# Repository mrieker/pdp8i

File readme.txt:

Re-implementation of a PDP-8/I processor using
currently available 74HC series DIP-form chips.
Includes extended arithmetic, 32KW memory and a
TTY interface.

Interfaces to a PiDP-8/I panel, taking the place of
the RasPI.

Optionally can use a ZTurn Zynq board to provide
additional I/O device emulation and TCL script
console access.  The Zynq also contains Verilog
equivalents of the circuit boards so can be used
for debugging and testing the board designs and
software with or without the physical circuit
boards.

Must have either the PiDP-8/I panel or the Zynq
board or both.

The circuit is a re-design using currently available
74AC, 74AHC and 74HC series chips.  It uses a 10MHz
signal for timing instead of delay lines.  It
preserves the TS1,TS2,TS3,TS4 timing states for the
most part.  In this design, TS1 takes 300nS (three
10MHz cycles), TS2,3,4 each take 400nS (four 10MHz
cycles), giving an overall cycle time of 1.5uS.

    TS1 - read memory into MBUF
    TS2 - compute memory update into MBUF
    TS3 - write memory from MBUF
          compute then write ACUM,LINK update
    TS4 - compute next major state
          including extended memory address

    The corresponding TPn occurs during last 100nS of
    the TSn.

If present, the ZTurn board provides the 10MHz signal,
allowing the Zynq full control of the clock for testing.
Otherwise it must on a separate board.

I/O instructions are also 1.5uS instead of being extended
to 4.25uS.  There is just one io pulse regardless of the
low three opcode bits that occurs starting 100nS into TS2
and ends at end of TS3.  I/O devices can use TP2 or TP3 to
clock data coming from the processor (from ACUM bus lines).
The processor clocks data from the I/O device (ACCLEAR,
INBUS, IOSKIP bus lines) at TP3.  An I/O device can extend
TS3 by asserting PAUSE starting in TS2.

The major states are the same (FETCH, DEFER, EXEC, WRDCT,
CURAD, BREAK), but with the addition of:

    INTAK - save and clear DF,IF registers, write PC to 00000,
            clear interrupt enable, jump to 00001
    DEPOS - do memory write in response to DEP switch
    EXAM  - do memory read in response to LDAD or EXAM switch

When halted, all four of TS1,2,3,4 are negated.  The state
info in the registers indicates what is going to happen next,
as halting occurs at the end of TS4 which establishes the next
major state.  Pressing CONT will start TS1 with whatever is in
the registers.

Directories:

    ccode    - C programs that run on the Zynq
    demos    - some PDP-8/I programs
    edu20c   - edusystem 20 basic
    kicads   - circuit boards
    verisim  - Verilator for testing circuit design
    zplin    - Zynq compatible Linux (softlink to pdp8l repo zplin)
    zynq     - Zynq Verilog code

Website:  https://www.outerworldapps.com/8ipics/

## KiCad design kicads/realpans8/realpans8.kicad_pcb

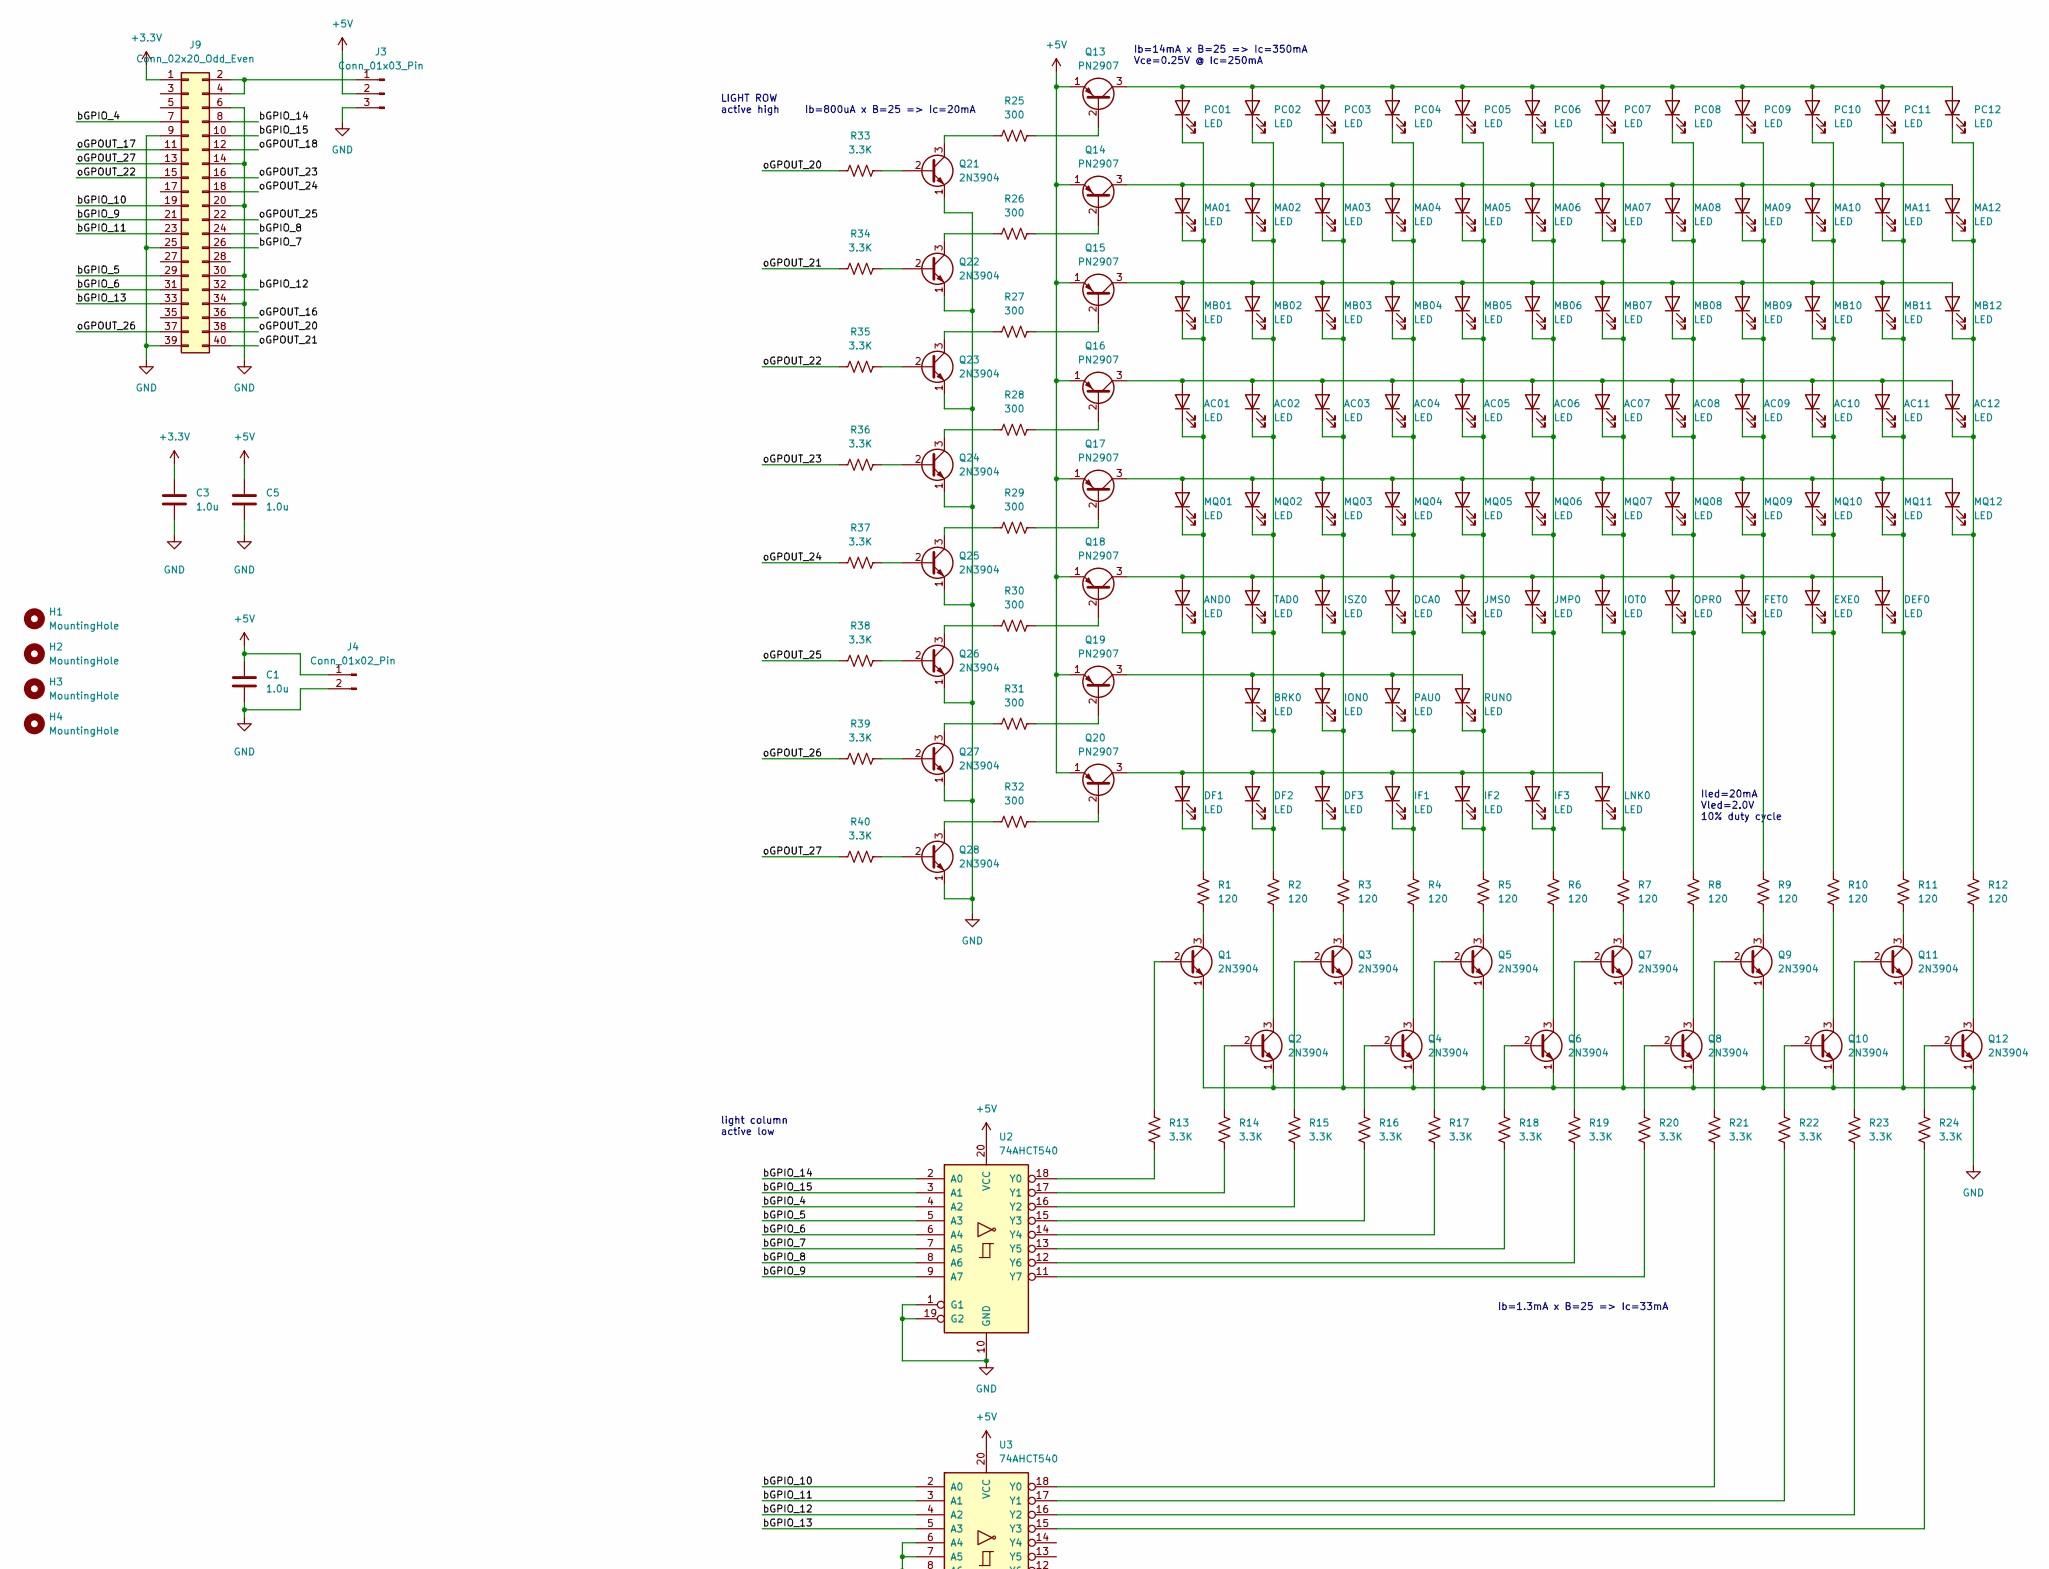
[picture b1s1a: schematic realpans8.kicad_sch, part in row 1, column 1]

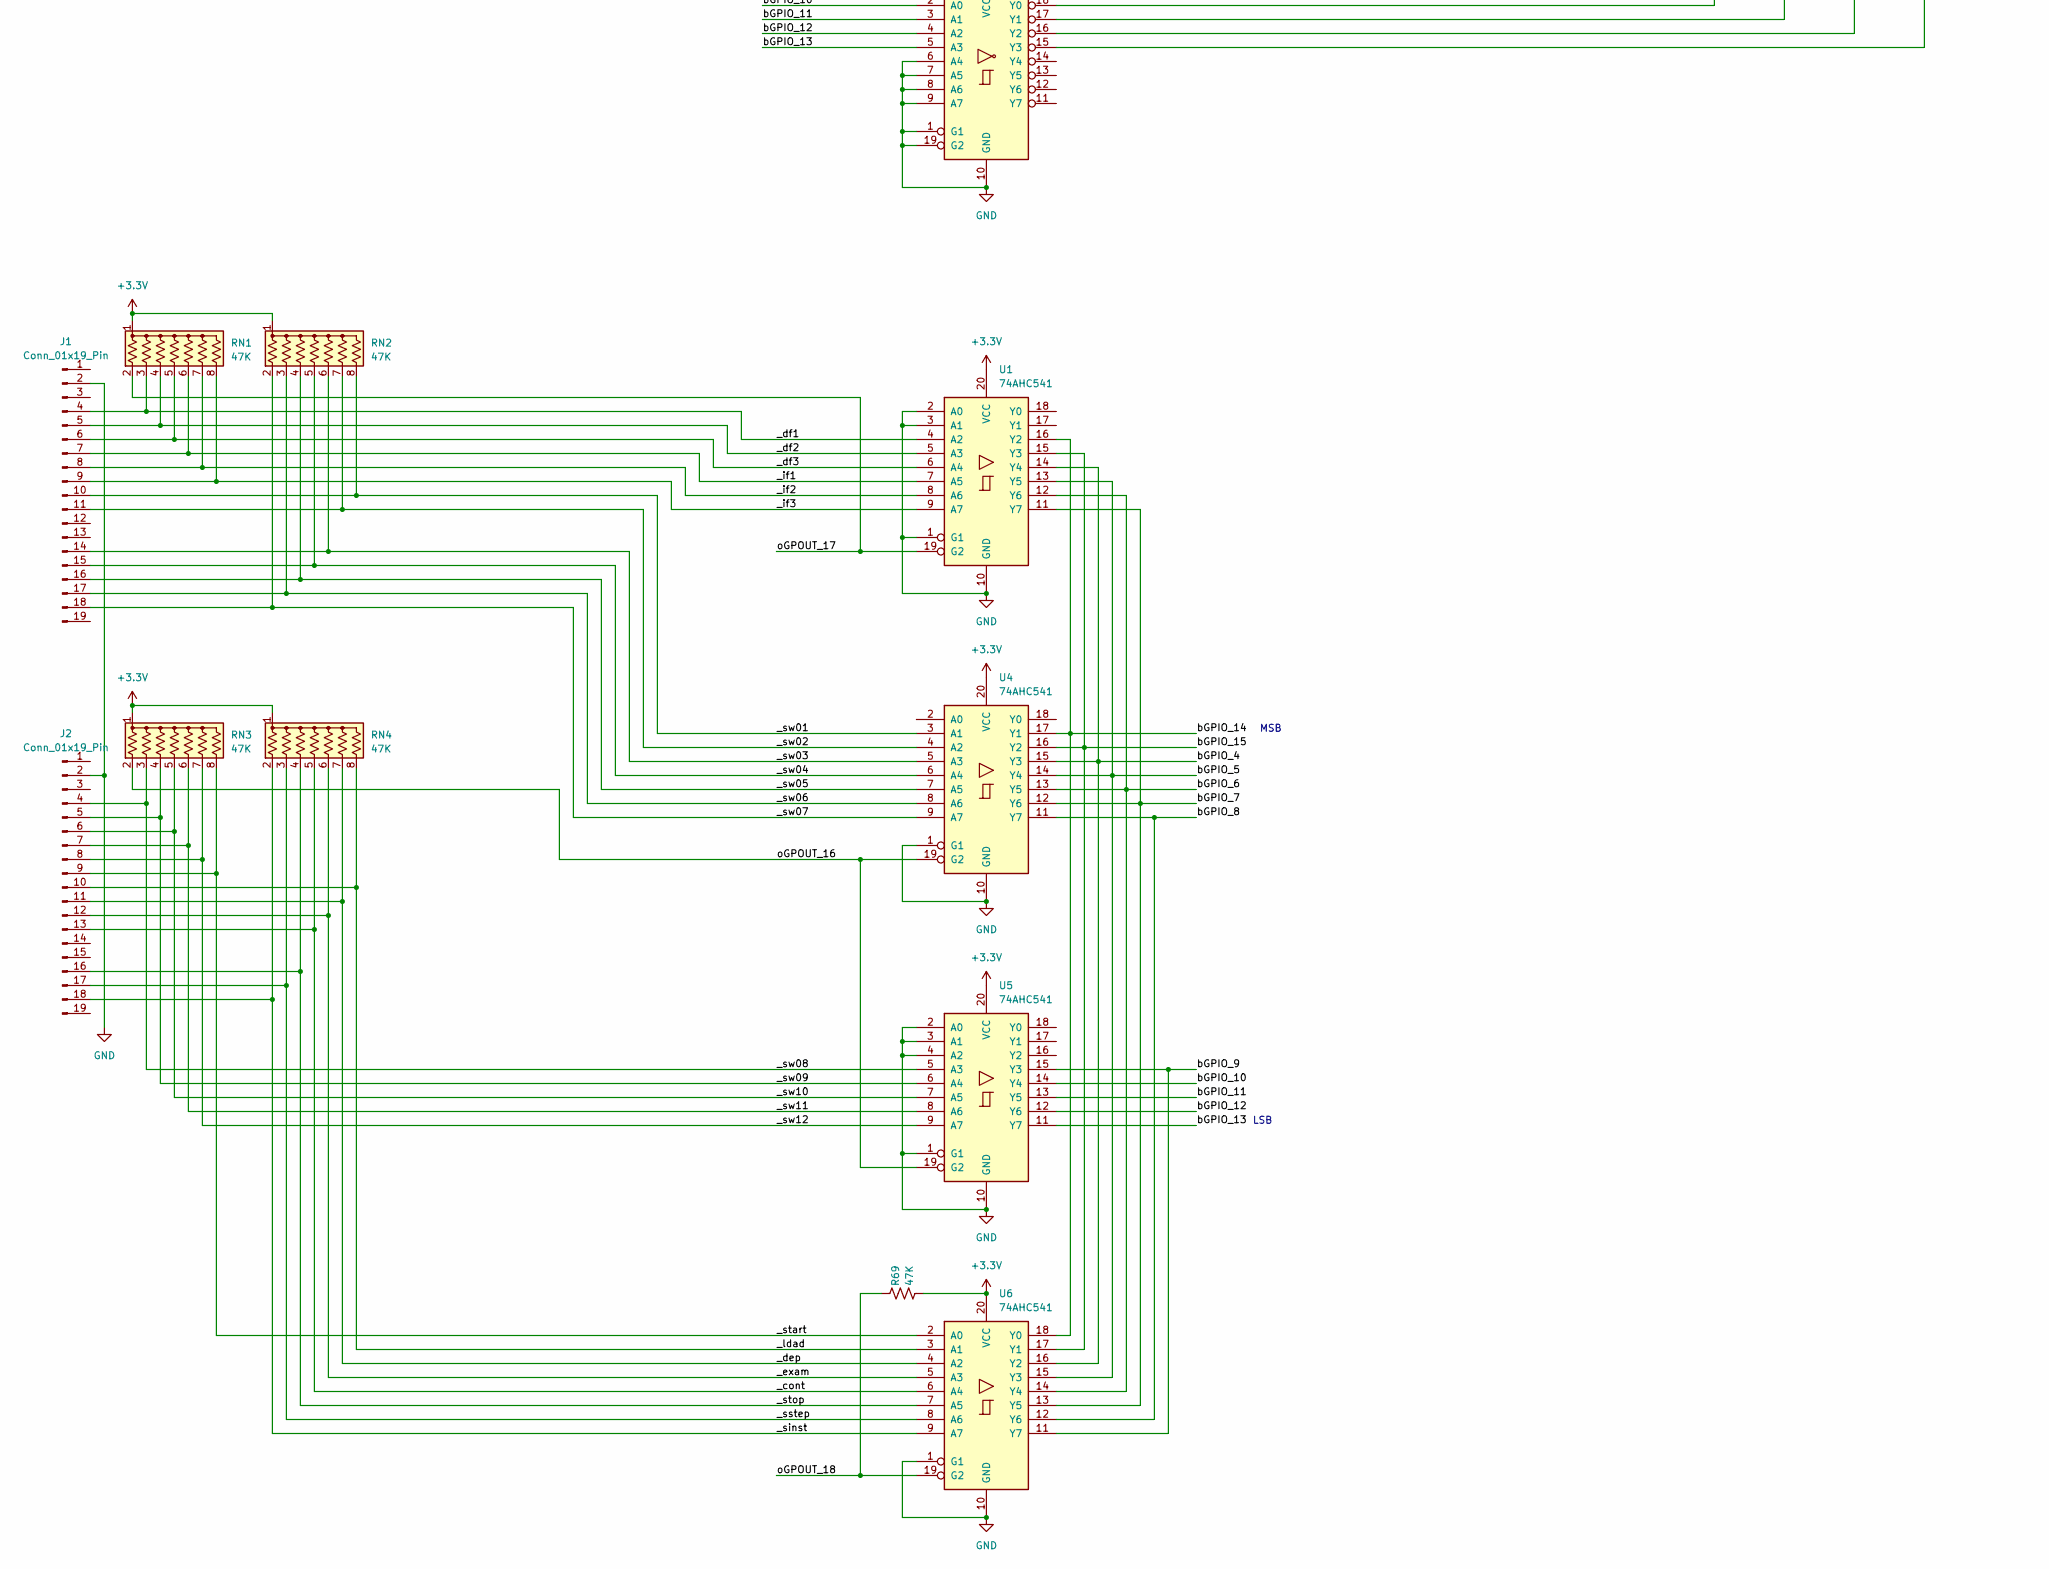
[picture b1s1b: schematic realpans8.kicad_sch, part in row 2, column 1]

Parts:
AC01, AC02, AC03, AC04, AC05, AC06, AC07, AC08, AC09, AC10, AC11, AC12: LED; LED_D5.0mm
AND0: LED; LED_D5.0mm
BRK0: LED; LED_D5.0mm
C1, C3, C5: 1.0u; R_Axial_DIN0207_L6.3mm_D2.5mm_P7.62mm_Horizontal
DCA0: LED; LED_D5.0mm
DEF0: LED; LED_D5.0mm
DF1, DF2, DF3: LED; LED_D5.0mm
EXE0: LED; LED_D5.0mm
FET0: LED; LED_D5.0mm
H1, H2, H3, H4: MountingHole; MountingHole_4.5mm
IF1, IF2, IF3: LED; LED_D5.0mm
ION0: LED; LED_D5.0mm
IOT0: LED; LED_D5.0mm
ISZ0: LED; LED_D5.0mm
J1, J2: Conn_01x19_Pin; PinHeader_1x19_P2.54mm_Vertical
J3: Conn_01x03_Pin; PinHeader_1x03_P2.54mm_Vertical
J4: Conn_01x02_Pin; PinHeader_1x02_P2.54mm_Vertical
J9: Conn_02x20_Odd_Even; PinHeader_2x20_P2.54mm_Vertical
JMP0: LED; LED_D5.0mm
JMS0: LED; LED_D5.0mm
LNK0: LED; LED_D5.0mm
MA01, MA02, MA03, MA04, MA05, MA06, MA07, MA08, MA09, MA10, MA11, MA12: LED; LED_D5.0mm
MB01, MB02, MB03, MB04, MB05, MB06, MB07, MB08, MB09, MB10, MB11, MB12: LED; LED_D5.0mm
MQ01, MQ02, MQ03, MQ04, MQ05, MQ06, MQ07, MQ08, MQ09, MQ10, MQ11, MQ12: LED; LED_D5.0mm
OPR0: LED; LED_D5.0mm
PAU0: LED; LED_D5.0mm
PC01, PC02, PC03, PC04, PC05, PC06, PC07, PC08, PC09, PC10, PC11, PC12: LED; LED_D5.0mm
Q1, Q2, Q3, Q4, Q5, Q6, Q7, Q8, Q9, Q10, Q11, Q12, Q21, Q22, Q23, Q24, Q25, Q26, Q27, Q28: 2N3904; TO-92_Wide
Q13, Q14, Q15, Q16, Q17, Q18, Q19, Q20: PN2907; TO-92_Wide
R1, R2, R3, R4, R5, R6, R7, R8, R9, R10, R11, R12: 120; R_Axial_DIN0207_L6.3mm_D2.5mm_P7.62mm_Horizontal
R13, R14, R15, R16, R17, R18, R19, R20, R21, R22, R23, R24, R33, R34, R35, R36, R37, R38, R39, R40: 3.3K; R_Axial_DIN0207_L6.3mm_D2.5mm_P7.62mm_Horizontal
R25, R26, R27, R28, R29, R30, R31, R32: 300; R_Axial_DIN0207_L6.3mm_D2.5mm_P7.62mm_Horizontal
R69: 47K; R_Axial_DIN0207_L6.3mm_D2.5mm_P7.62mm_Horizontal
RN1, RN2, RN3, RN4: 47K; R_Array_SIP8
RUN0: LED; LED_D5.0mm
TAD0: LED; LED_D5.0mm
U1, U4, U5, U6: 74AHC541; DIP-20_W7.62mm
U2, U3: 74AHCT540; DIP-20_W7.62mm

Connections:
+3.3V: C3.1, J9.1, R69.1, RN1.1 (common), RN2.1 (common), RN3.1 (common), RN4.1 (common), U1.20 (VCC), U4.20 (VCC), U5.20 (VCC), U6.20 (VCC)
+5V: C1.1, C5.1, J3.2, J4.1, Q13.1 (E), Q14.1 (E), Q15.1 (E), Q16.1 (E), Q17.1 (E), Q18.1 (E), Q19.1 (E), Q20.1 (E), U2.20 (VCC), U3.20 (VCC)
/_cont: J2.13, RN4.5 (R4), U6.6 (A4)
/_dep: J2.11, RN4.7 (R6), U6.4 (A2)
/_df1: J1.4, RN1.3 (R2), U1.4 (A2)
/_df2: J1.5, RN1.4 (R3), U1.5 (A3)
/_df3: J1.6, RN1.5 (R4), U1.6 (A4)
/_exam: J2.12, RN4.6 (R5), U6.5 (A3)
/_if1: J1.7, RN1.6 (R5), U1.7 (A5)
/_if2: J1.8, RN1.7 (R6), U1.8 (A6)
/_if3: J1.9, RN1.8 (R7), U1.9 (A7)
/_ldad: J2.10, RN4.8 (R7), U6.3 (A1)
/_sinst: J2.18, RN4.2 (R1), U6.9 (A7)
/_sstep: J2.17, RN4.3 (R2), U6.8 (A6)
/_start: J2.9, RN3.8 (R7), U6.2 (A0)
/_stop: J2.16, RN4.4 (R3), U6.7 (A5)
/_sw01: J1.10, RN2.8 (R7), U4.3 (A1)
/_sw02: J1.11, RN2.7 (R6), U4.4 (A2)
/_sw03: J1.14, RN2.6 (R5), U4.5 (A3)
/_sw04: J1.15, RN2.5 (R4), U4.6 (A4)
/_sw05: J1.16, RN2.4 (R3), U4.7 (A5)
/_sw06: J1.17, RN2.3 (R2), U4.8 (A6)
/_sw07: J1.18, RN2.2 (R1), U4.9 (A7)
/_sw08: J2.4, RN3.3 (R2), U5.5 (A3)
/_sw09: J2.5, RN3.4 (R3), U5.6 (A4)
/_sw10: J2.6, RN3.5 (R4), U5.7 (A5)
/_sw11: J2.7, RN3.6 (R5), U5.8 (A6)
/_sw12: J2.8, RN3.7 (R6), U5.9 (A7)
/bGPIO_4: J9.7, U1.14 (Y4), U2.4 (A2), U4.15 (Y3), U6.16 (Y2)
/bGPIO_5: J9.29, U1.13 (Y5), U2.5 (A3), U4.14 (Y4), U6.15 (Y3)
/bGPIO_6: J9.31, U1.12 (Y6), U2.6 (A4), U4.13 (Y5), U6.14 (Y4)
/bGPIO_7: J9.26, U1.11 (Y7), U2.7 (A5), U4.12 (Y6), U6.13 (Y5)
/bGPIO_8: J9.24, U2.8 (A6), U4.11 (Y7), U6.12 (Y6)
/bGPIO_9: J9.21, U2.9 (A7), U5.15 (Y3), U6.11 (Y7)
/bGPIO_10: J9.19, U3.2 (A0), U5.14 (Y4)
/bGPIO_11: J9.23, U3.3 (A1), U5.13 (Y5)
/bGPIO_12: J9.32, U3.4 (A2), U5.12 (Y6)
/bGPIO_13: J9.33, U3.5 (A3), U5.11 (Y7)
/bGPIO_14: J9.8, U1.16 (Y2), U2.2 (A0), U4.17 (Y1), U6.18 (Y0)
/bGPIO_15: J9.10, U1.15 (Y3), U2.3 (A1), U4.16 (Y2), U6.17 (Y1)
/oGPOUT_16: J9.36, RN3.2 (R1), U4.19 (G2), U5.19 (G2)
/oGPOUT_17: J9.11, RN1.2 (R1), U1.19 (G2)
/oGPOUT_18: J9.12, R69.2, U6.19 (G2)
/oGPOUT_20: J9.38, R33.1
/oGPOUT_21: J9.40, R34.1
/oGPOUT_22: J9.15, R35.1
/oGPOUT_23: J9.16, R36.1
/oGPOUT_24: J9.18, R37.1
/oGPOUT_25: J9.22, R38.1
/oGPOUT_26: J9.37, R39.1
/oGPOUT_27: J9.13, R40.1
GND: C1.2, C3.2, C5.2, J1.2, J2.2, J3.3, J4.2, J9.6, J9.9, J9.14, J9.20, J9.25, J9.30, J9.34, J9.39, Q1.1 (E), Q2.1 (E), Q3.1 (E), Q4.1 (E), Q5.1 (E), Q6.1 (E), Q7.1 (E), Q8.1 (E), Q9.1 (E), Q10.1 (E), Q11.1 (E), Q12.1 (E), Q21.1 (E), Q22.1 (E), Q23.1 (E), Q24.1 (E), Q25.1 (E), Q26.1 (E), Q27.1 (E), Q28.1 (E), U1.1 (G1), U1.2 (A0), U1.3 (A1), U1.10 (GND), U2.1 (G1), U2.10 (GND), U2.19 (G2), U3.1 (G1), U3.6 (A4), U3.7 (A5), U3.8 (A6), U3.9 (A7), U3.10 (GND), U3.19 (G2), U4.1 (G1), U4.10 (GND), U5.1 (G1), U5.2 (A0), U5.3 (A1), U5.4 (A2), U5.10 (GND), U6.1 (G1), U6.10 (GND)
unnamed: AC01.2 (A), AC02.2 (A), AC03.2 (A), AC04.2 (A), AC05.2 (A), AC06.2 (A), AC07.2 (A), AC08.2 (A), AC09.2 (A), AC10.2 (A), AC11.2 (A), AC12.2 (A), Q16.3 (C)
unnamed: AC01.1 (K), AND0.1 (K), DF1.1 (K), MA01.1 (K), MB01.1 (K), MQ01.1 (K), PC01.1 (K), R1.1
unnamed: AC02.1 (K), BRK0.1 (K), DF2.1 (K), MA02.1 (K), MB02.1 (K), MQ02.1 (K), PC02.1 (K), R2.1, TAD0.1 (K)
unnamed: AC03.1 (K), DF3.1 (K), ION0.1 (K), ISZ0.1 (K), MA03.1 (K), MB03.1 (K), MQ03.1 (K), PC03.1 (K), R3.1
unnamed: AC04.1 (K), DCA0.1 (K), IF1.1 (K), MA04.1 (K), MB04.1 (K), MQ04.1 (K), PAU0.1 (K), PC04.1 (K), R4.1
unnamed: AC05.1 (K), IF2.1 (K), JMS0.1 (K), MA05.1 (K), MB05.1 (K), MQ05.1 (K), PC05.1 (K), R5.1, RUN0.1 (K)
unnamed: AC06.1 (K), IF3.1 (K), JMP0.1 (K), MA06.1 (K), MB06.1 (K), MQ06.1 (K), PC06.1 (K), R6.1
unnamed: AC07.1 (K), IOT0.1 (K), LNK0.1 (K), MA07.1 (K), MB07.1 (K), MQ07.1 (K), PC07.1 (K), R7.1
unnamed: AC08.1 (K), MA08.1 (K), MB08.1 (K), MQ08.1 (K), OPR0.1 (K), PC08.1 (K), R8.1
unnamed: AC09.1 (K), FET0.1 (K), MA09.1 (K), MB09.1 (K), MQ09.1 (K), PC09.1 (K), R9.1
unnamed: AC10.1 (K), EXE0.1 (K), MA10.1 (K), MB10.1 (K), MQ10.1 (K), PC10.1 (K), R10.1
unnamed: AC11.1 (K), DEF0.1 (K), MA11.1 (K), MB11.1 (K), MQ11.1 (K), PC11.1 (K), R11.1
unnamed: AC12.1 (K), MA12.1 (K), MB12.1 (K), MQ12.1 (K), PC12.1 (K), R12.1
unnamed: AND0.2 (A), DCA0.2 (A), DEF0.2 (A), EXE0.2 (A), FET0.2 (A), IOT0.2 (A), ISZ0.2 (A), JMP0.2 (A), JMS0.2 (A), OPR0.2 (A), Q18.3 (C), TAD0.2 (A)
unnamed: BRK0.2 (A), ION0.2 (A), PAU0.2 (A), Q19.3 (C), RUN0.2 (A)
unnamed: DF1.2 (A), DF2.2 (A), DF3.2 (A), IF1.2 (A), IF2.2 (A), IF3.2 (A), LNK0.2 (A), Q20.3 (C)
unnamed: J3.1, J9.2, J9.4
unnamed: MA01.2 (A), MA02.2 (A), MA03.2 (A), MA04.2 (A), MA05.2 (A), MA06.2 (A), MA07.2 (A), MA08.2 (A), MA09.2 (A), MA10.2 (A), MA11.2 (A), MA12.2 (A), Q14.3 (C)
unnamed: MB01.2 (A), MB02.2 (A), MB03.2 (A), MB04.2 (A), MB05.2 (A), MB06.2 (A), MB07.2 (A), MB08.2 (A), MB09.2 (A), MB10.2 (A), MB11.2 (A), MB12.2 (A), Q15.3 (C)
unnamed: MQ01.2 (A), MQ02.2 (A), MQ03.2 (A), MQ04.2 (A), MQ05.2 (A), MQ06.2 (A), MQ07.2 (A), MQ08.2 (A), MQ09.2 (A), MQ10.2 (A), MQ11.2 (A), MQ12.2 (A), Q17.3 (C)
unnamed: PC01.2 (A), PC02.2 (A), PC03.2 (A), PC04.2 (A), PC05.2 (A), PC06.2 (A), PC07.2 (A), PC08.2 (A), PC09.2 (A), PC10.2 (A), PC11.2 (A), PC12.2 (A), Q13.3 (C)
unnamed: Q1.2 (B), R13.1
unnamed: Q1.3 (C), R1.2
unnamed: Q2.2 (B), R14.1
unnamed: Q2.3 (C), R2.2
unnamed: Q3.2 (B), R15.1
unnamed: Q3.3 (C), R3.2
unnamed: Q4.2 (B), R16.1
unnamed: Q4.3 (C), R4.2
unnamed: Q5.2 (B), R17.1
unnamed: Q5.3 (C), R5.2
unnamed: Q6.2 (B), R18.1
unnamed: Q6.3 (C), R6.2
unnamed: Q7.2 (B), R19.1
unnamed: Q7.3 (C), R7.2
unnamed: Q8.2 (B), R20.1
unnamed: Q8.3 (C), R8.2
unnamed: Q9.2 (B), R21.1
unnamed: Q9.3 (C), R9.2
unnamed: Q10.2 (B), R22.1
unnamed: Q10.3 (C), R10.2
unnamed: Q11.2 (B), R23.1
unnamed: Q11.3 (C), R11.2
unnamed: Q12.2 (B), R24.1
unnamed: Q12.3 (C), R12.2
unnamed: Q13.2 (B), R25.2
unnamed: Q14.2 (B), R26.2
unnamed: Q15.2 (B), R27.2
unnamed: Q16.2 (B), R28.2
unnamed: Q17.2 (B), R29.2
unnamed: Q18.2 (B), R30.2
unnamed: Q19.2 (B), R31.2
unnamed: Q20.2 (B), R32.2
unnamed: Q21.2 (B), R33.2
unnamed: Q21.3 (C), R25.1
unnamed: Q22.2 (B), R34.2
unnamed: Q22.3 (C), R26.1
unnamed: Q23.2 (B), R35.2
unnamed: Q23.3 (C), R27.1
unnamed: Q24.2 (B), R36.2
unnamed: Q24.3 (C), R28.1
unnamed: Q25.2 (B), R37.2
unnamed: Q25.3 (C), R29.1
unnamed: Q26.2 (B), R38.2
unnamed: Q26.3 (C), R30.1
unnamed: Q27.2 (B), R39.2
unnamed: Q27.3 (C), R31.1
unnamed: Q28.2 (B), R40.2
unnamed: Q28.3 (C), R32.1
unnamed: R13.2, U2.18 (Y0)
unnamed: R14.2, U2.17 (Y1)
unnamed: R15.2, U2.16 (Y2)
unnamed: R16.2, U2.15 (Y3)
unnamed: R17.2, U2.14 (Y4)
unnamed: R18.2, U2.13 (Y5)
unnamed: R19.2, U2.12 (Y6)
unnamed: R20.2, U2.11 (Y7)
unnamed: R21.2, U3.18 (Y0)
unnamed: R22.2, U3.17 (Y1)
unnamed: R23.2, U3.16 (Y2)
unnamed: R24.2, U3.15 (Y3)

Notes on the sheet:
Ib=1.3mA x B=25 => Ic=33mA
Iled=20mA Vled=2.0V 10% duty cycle
Ib=800uA x B=25 => Ic=20mA
MSB
Ib=14mA x B=25 => Ic=350mA Vce=0.25V @ Ic=250mA
LIGHT ROW active high
light column active low
LSB

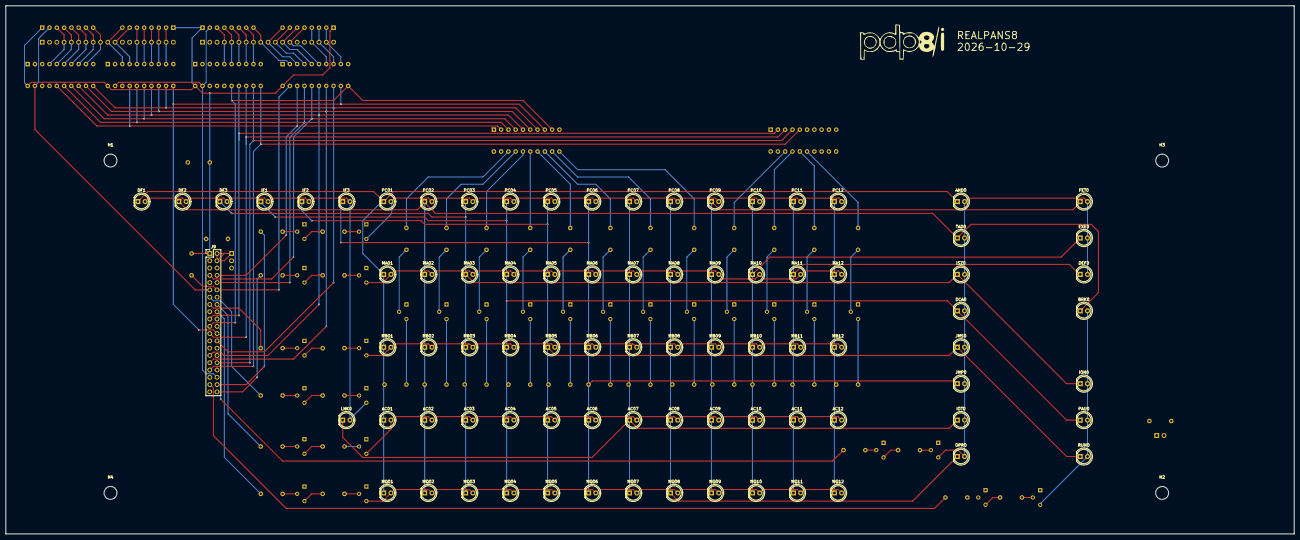
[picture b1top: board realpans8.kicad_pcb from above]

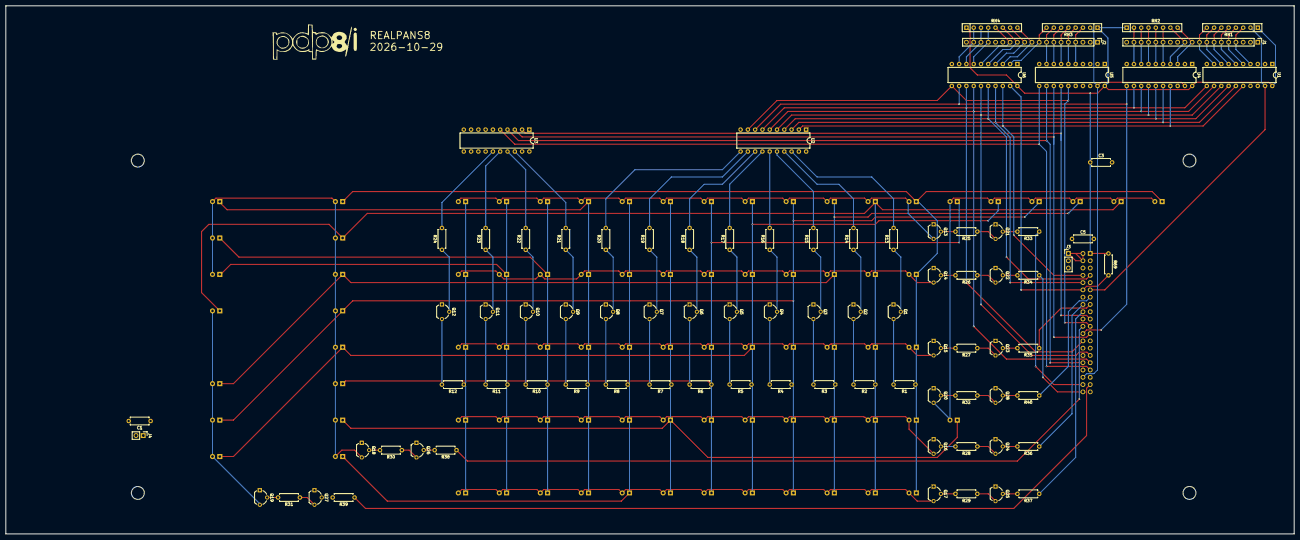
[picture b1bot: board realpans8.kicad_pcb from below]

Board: 4 copper layers, 449.3 x 184.2 mm, 173 parts (86 on the bottom side), 133 nets.

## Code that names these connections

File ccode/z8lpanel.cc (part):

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        // read bulbs and switches
        padlib->readpads (&pads);

        bool irand = pads.light.ir == 0;
        bool irtad = pads.light.ir == 1;
        bool irisz = pads.light.ir == 2;
        bool irdca = pads.light.ir == 3;
        bool irjms = pads.light.ir == 4;
        bool irjmp = pads.light.ir == 5;
        bool iriot = pads.light.ir == 6;
        bool iropr = pads.light.ir == 7;

        bool msfet = pads.light.ms == MS_FETCH;
        bool msdef = pads.light.ms == MS_DEFER;
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
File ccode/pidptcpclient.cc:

//    Copyright (C) Mike Rieker, Beverly, MA USA
//    www.outerworldapps.com
//
//    This program is free software; you can redistribute it and/or modify
//    it under the terms of the GNU General Public License as published by
//    the Free Software Foundation; version 2 of the License.
//
//    This program is distributed in the hope that it will be useful,
//    but WITHOUT ANY WARRANTY; without even the implied warranty of
//    MERCHANTABILITY or FITNESS FOR A PARTICULAR PURPOSE.  See the
//    GNU General Public License for more details.
//
//    EXPECT it to FAIL when someone's HeALTh or PROpeRTy is at RISk.
//
//    You should have received a copy of the GNU General Public License
//    along with this program; if not, write to the Free Software
//    Foundation, Inc., 59 Temple Place, Suite 330, Boston, MA  02111-1307  USA
//
//    http://www.gnu.org/licenses/gpl-2.0.html

// runs on zynq to send lights to and receive switches from raspi plugged into pidp8i panel
// this is a different pidp8i panel than one plugged into console.kicad_sch board

// on raspi:
//  ./pidptcpserver

// on zynq:
//  ./pidptcpclient [-nomqsc] <raspihostname>

#include <signal.h>
#include <string.h>
#include <time.h>

#include "i2czlib.h"
#include "pidp.h"
#include "z8idefs.h"

// gpio pins

                    //  LR1 LR2 LR3 LR4 LR5 LR6 LR7 LR8 SR1 SR2 SR3
#define COL1    14  //  pc1 ma1 mb1 ac1 mq1 and cad df1 sw1 df1 start   [MSB]
#define COL2    15  //  pc2 ma2 mb2 ac2 mq2 tad brk df2 sw2 df2 ldaddr
#define COL3     4  //  pc3 ma3 mb3 ac3 mq3 isz ion df3 sw3 df3 dep
#define COL4     5  //   .   .   .   .   .  dca pau if1  .  if1 exam
#define COL5     6  //   .   .   .   .   .  jms run if2  .  if2 cont
#define COL6     7  //   .   .   .   .   .  jmp sc1 if3  .  if3 stop
#define COL7     8  //   .   .   .   .   .  iot sc2 lnk  .      sstep
#define COL8     9  //   .   .   .   .   .  opr sc3      .      sinst
#define COL9    10  //   .   .   .   .   .  fet sc4      .
#define COL10   11  //   .   .   .   .   .  exe sc5      .
#define COL11   12  //   .   .   .   .   .  def          .
#define COL12   13  //   .   .   .   .   .  wct          .              [LSB]

#define COLMIN 4

static bool volatile ctrlcflag;
static uint16_t ledscrams[4096];
static uint16_t opcodeleds[8];
static uint16_t swunscrams[65536>>COLMIN];

static void siginthand (int signum);

int main (int argc, char **argv)
{
    setlinebuf (stdout);

    bool nomqsc = false;
    char const *server = NULL;
    for (int i = 0; ++ i < argc;) {
        if (strcasecmp (argv[i], "-nomqsc") == 0) {
            nomqsc = true;
            continue;
        }
        if (argv[i][0] == '-') {
            fprintf (stderr, "unknown option %s\n", argv[i]);
            return 1;
        }
        if (server != NULL) {
            fprintf (stderr, "unknown parameter %s\n", argv[i]);
            return 1;
        }
        server = argv[i];
    }
    if (server == NULL) {
        fprintf (stderr, "missing server hostname\n");
        return 1;
    }
    pidp_open (server);

    opcodeleds[0] = 1 << COL1;
    opcodeleds[1] = 1 << COL2;
    opcodeleds[2] = 1 << COL3;
    opcodeleds[3] = 1 << COL4;
    opcodeleds[4] = 1 << COL5;
    opcodeleds[5] = 1 << COL6;
    opcodeleds[6] = 1 << COL7;
    opcodeleds[7] = 1 << COL8;

    for (uint16_t data = 0; data <= 07777; data ++) {
        uint16_t gpio = 0;
        if (data & 04000) gpio |= 1 << COL1;
        if (data & 02000) gpio |= 1 << COL2;
        if (data & 01000) gpio |= 1 << COL3;
        if (data & 00400) gpio |= 1 << COL4;
        if (data & 00200) gpio |= 1 << COL5;
        if (data & 00100) gpio |= 1 << COL6;
        if (data & 00040) gpio |= 1 << COL7;
        if (data & 00020) gpio |= 1 << COL8;
        if (data & 00010) gpio |= 1 << COL9;
        if (data & 00004) gpio |= 1 << COL10;
        if (data & 00002) gpio |= 1 << COL11;
        if (data & 00001) gpio |= 1 << COL12;
        ledscrams[data] = gpio;
        swunscrams[gpio>>COLMIN] = data;
    }

    // access FPGA I2C interface to console board
    I2CZLib i2czlib;
    Z8IPanel pads;
    memset (&pads, 0, sizeof pads);

    signal (SIGINT,  siginthand);
    signal (SIGTERM, siginthand);

    i2czlib.lockpads ();

    bool firstswrow = true;
    uint16_t lastswrows[3];
    memset (lastswrows, 0, sizeof lastswrows);

    PiDPMsg pidpmsg;
    memset (&pidpmsg, 0, sizeof pidpmsg);

    while (! ctrlcflag) {

        // read lights from fpga
        i2czlib.readpads (&pads, false);
        i2czlib.unlkpads ();

        // send lights over tcp to pidp panel
        pidpmsg.ledrows[0] = ledscrams[pads.light.pc];
        pidpmsg.ledrows[1] = ledscrams[pads.light.ma];
        pidpmsg.ledrows[2] = ledscrams[pads.light.mb];
        pidpmsg.ledrows[3] = ledscrams[pads.light.ac];
        if (! nomqsc) {
            pidpmsg.ledrows[4] = ledscrams[pads.light.mq];
        }

        pidpmsg.ledrows[5] =
            opcodeleds[pads.light.ir] |
            ((pads.light.ms == MS_FETCH) ? (1 << COL9)  : 0) |
            ((pads.light.ms == MS_EXEC)  ? (1 << COL10) : 0) |
            ((pads.light.ms == MS_DEFER) ? (1 << COL11) : 0) |
            ((pads.light.ms == MS_WRDCT) ? (1 << COL12) : 0);

        pidpmsg.ledrows[6] =
            ((pads.light.ms == MS_CURAD) ? (1 << COL1) : 0) |
            ((pads.light.ms == MS_BREAK) ? (1 << COL2) : 0) |
            (pads.light.ion ? (1 << COL3) : 0) |
            (pads.light.pau ? (1 << COL4) : 0) |
            (pads.light.run ? (1 << COL5) : 0);
        if (! nomqsc) {
            pidpmsg.ledrows[6] |= ledscrams[pads.light.sc<<2];
        }

        pidpmsg.ledrows[7] =
            ledscrams[(pads.light.dfld<<9)|(pads.light.ifld<<6)] |
            (pads.light.link ? (1 << COL7) : 0);

        // ... also receives switches from pidp panel
        if (! pidp_proc (&pidpmsg)) continue;

        i2czlib.lockpads ();

        // only send switches to fpga if there is a change
        // - this allows other things (like tcl scripts) to use switches
        // - and it takes over the switches only when someone is using them
        if (! firstswrow && ((pidpmsg.swrows[0] != lastswrows[0]) ||
                (pidpmsg.swrows[1] != lastswrows[1]) || (pidpmsg.swrows[2] != lastswrows[2]))) {

            // send all switches to fpga
            pads.togval.reg = swunscrams[pidpmsg.swrows[0]>>COLMIN];
            uint32_t sr2 = swunscrams[pidpmsg.swrows[1]>>COLMIN];
            pads.togval.dfld  = (sr2 >> 9) & 7;
            pads.togval.ifld  = (sr2 >> 6) & 7;
            pads.togval.sinst = (pidpmsg.swrows[2] >> COL8) & 1;
            pads.togval.sstep = (pidpmsg.swrows[2] >> COL7) & 1;
            pads.button.stop  = (pidpmsg.swrows[2] >> COL6) & 1;
            pads.button.cont  = (pidpmsg.swrows[2] >> COL5) & 1;
            pads.button.start = (pidpmsg.swrows[2] >> COL1) & 1;
            pads.button.ldad  = (pidpmsg.swrows[2] >> COL2) & 1;
            pads.button.exam  = (pidpmsg.swrows[2] >> COL4) & 1;
            pads.button.depos = (pidpmsg.swrows[2] >> COL3) & 1;
            pads.togovr.reg   = 07777;
            pads.togovr.dfld  = 7;
            pads.togovr.ifld  = 7;
            pads.togovr.sinst = true;
            pads.togovr.sstep = true;

            uint32_t now = time (NULL);
            printf ("%02u:%02u:%02u   %o %o  %04o  %s %s %s %s %s %s %s %s\n",
                now / 3600 % 24, now / 60 % 60, now % 60,
                pads.togval.dfld, pads.togval.ifld, pads.togval.reg,
                pads.button.start ? "START" : "     ",
                pads.button.ldad  ? "LDAD"  : "    ",
                pads.button.depos ? "DEPOS" : "     ",
                pads.button.exam  ? "EXAM"  : "    ",
                pads.button.cont  ? "CONT"  : "    ",
                pads.button.stop  ? "STOP"  : "    ",
                pads.togval.sstep ? "SSTEP" : "     ",
                pads.togval.sinst ? "SINST" : "     ");

            i2czlib.writepads (&pads);
        }
        firstswrow = false;
        lastswrows[0] = pidpmsg.swrows[0];
        lastswrows[1] = pidpmsg.swrows[1];
        lastswrows[2] = pidpmsg.swrows[2];
    }

    i2czlib.unlkpads ();

    return 0;
}

static void siginthand (int signum)
{
    if (ctrlcflag) exit (1);
    ctrlcflag = true;
}

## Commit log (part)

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2026-02-03 initial commit
    $ cd verisim
    $ ./verimain.x86_64
    > isztest
    > startat 0100
    > runloop 1000000
    > runloop 1000000
2026-02-04 add simtest.sh and simtest.tcl simulator test script
    runs simulator with random instructions
    also includes assemble and disassemble TCL commands
2026-02-05 fill out field selection in processor.v
2026-02-06 get HLT simtest working
    and fix IOP2/IOP4 overlap
    clean up some simtest.tcl code
2026-02-06 move randbits to C code
    seems TCL has memory leakage issues with 64-bit numbers
2026-02-07 move all address changes to TP4
    ...so memory has constant address during TS3
2026-02-07 more timing simplification
    TS1:
    read memory
    TP1:
    clock memory data into MBUF
    TS2:
    compute updates for MBUF, PCTR
2026-02-08 regroup things around in processor.v
    gather all the loading of a register together
    to make it more like an hardware implementation
2026-02-10 add extended arithmetic support to processor
    expects ext arith board to process opcode and put result on io bus by TP3
    in either FETCH (non-memory opcode) or EXEC cycle (with memory opcode)
2026-02-11 add extarith.v module and get it working
2026-02-13 clean up clock and reset signals
    clok2 = 10MHz clock signal
    reset = power-on reset signal
2026-02-15 fix iopn signal generation
    include masking with instruction bits
2026-02-26 simplify timing cycle
    just have one iop and it overlaps TS2+TS3
    ...so all cycles are 1.6uS
2026-02-26 remove jmpjms factor from intinh test in processor.v
    intinh is now cleared in TP3 but not tested until TP4
2026-03-11 eliminate prod register from extarith.v
    also adds original AC value to product
    like pdp-8/v which passes D0MB maindec
2026-03-12 get a few more instructions of simtest.sh working
2026-03-12 get a couple instructions working with verisim/simtest.sh script
2026-03-12 get more cycles working in processor.kicad_sch and registers.kicad_sch
2026-03-12 get HLT opcode to work
    CONT switch used to wipe out non-FETCH state (such as WRDCT or BREAK)
2026-03-12 get OSR working
2026-03-12 add test code for ldad,depos,exam switches
2026-03-12 combine registers onto processor circuit board
    none of the console stuff works though
    will have to rebuild it
2026-03-12 get OSR instruction working again
2026-03-12 some circuit simplifications
2026-03-12 get all switches working in processor schematic
2026-03-12 connect up power connections to chips on processor board
2026-03-12 get extmemory working
    - runs simtest.sh 80M+ cycles
    have to run make command twice (get UNOPTFLAG warnings first time)
2026-03-12 get more of extmemory board working
2026-03-12 get start button working
2026-03-14 get a little more of new extarith.v working
2026-03-15 get new extarith divide working
2026-03-15 clean up using sctr for all counting like pdp-8/e
    use descriptions in small computer handbook 1973 chap 5
2026-03-17 upadte extarith.v muxes to be more 74xx chip-like
    also rename hold => pause
2026-03-18 stretch multiply & divide cycles to 300nS
    also allow 300nS for divide overflow
2026-03-19 add extarith schematic
    doesn't work yet
2026-03-19 program in 10nS delay per gate in verilog simulation
    removed testing of extarith for now
2026-03-20 change cycles times to 120nS
    ...addition takes too long
2026-03-20 fix up console switch timing in processor
    ldad/exam/dep:
    on press,
    set up alu to generate new MADR then after 300nS pulse it in
    then after another 100nS, load new state in MAJST
    on release,
    clear HREQ to perform the cycle
2026-03-20 set TS1=300nS, TS2=500nS, TS3=500nS, TS4=300nS
    adding only done in TS2,TS3 so make them longer
    others can be short
2026-03-21 add console circuit board
    (slows simtest.tcl down quite a bit)
2026-03-22 get console board working
2026-03-24 eliminate dependency on digging latched swreg value from internal console module signals
2026-03-24 add oscillator chip to console board
    also handle net names with < = > (used by 7485)
2026-03-25 add zynq files to access backplane simulation file
2026-03-26 get zynq stuff to compile and modify verimain to access it
    don't have driver to access page yet
2026-03-26 add km-zynqpdp8i driver to access zynq register page
    runs simtest.sh on zynq
2026-03-27 remove verisim .v files that are superceded by kicad-derived .v files
2026-03-28 add tty to zynq and get lights working in verilator
2026-03-28 get pdp8itty working in verilator
2026-03-29 get D01B maindec working with verilator
2026-04-06 add mcp23017 chip to console board
    test access to 23017:
    $ ./verimain
    ;# write 32->reg 0; 45->reg 1
    > iic wr 0x40 wr 0 wr 0x32 wr 0x45
    > clk 11111
    11111
2026-04-11 get simtest.sh working with MCP23017 console chip
    export usemcp=1
    ./simtest.sh
2026-04-12 allow console mcp23017 to read panel switches
    test:
    usemcp=0 ./simtest.sh gpio connector only
    lights: bus -> muxes -> gpio -> test script
    switches: test script -> gpio -> flipflops -> bus
    usemcp=1 ./simtest.sh mcp23017 only (gpio gets lights but not switches)
    lights: bus -> muxes -> gpio,mcp23017 -> test script
2026-04-22 little fix to simtest.tcl
    defer requesting dma or interrupt
2026-04-23 merge DMADR[11:00] bus into INBUS
    DMA master only needs to output the address during TS4
    and nothing else uses INBUS during that time
2026-04-25 put buffers on all bus pins
    make the signals active low so can put pullup terminators on backplane
    doesn't work yet
2026-04-26 get a few ./simtest.sh instructions working
2026-04-26 get a few more ./simtest.sh instructions working
2026-04-27 get usemcp=1,2 modes working with simtest.sh
    need to set gpio panel connector data bits to all ones so
    they don't interfere with console.kicad_sch bGPIO data bits
2026-04-27 add BRKGNTI/BRKGNTO signals to bus
    set at TP3 of all cycles to match BRKRQST line
    cleared at TP2 in BREAK cycle
2026-05-02 have armwrite self clock so don't need to advance processor state
2026-05-02 get started on doing better gate/flipflop delays
    doesn't work
2026-05-03 get some more working with new clocking
    run with clkratio=24
    simtest.sh runs 1259 cycles
2026-05-04 account for setup time in flipflop chips
    export clkratio=40
    export testexar=1
    export usemcp=0
    ./simtest.sh
2026-05-06 add back a version of chips.v that has fixed 10nS delay
    also put cycle counter in dmatest.v for testing
2026-05-07 add BRKCYC signal to bus for DMA circuits
    glitch-free indicating break cycle in progress
    sets at beginning of TS1, clears at end of TS3
2026-05-08 small delay when switching busDFLD/busIFLD for LDAD switch
    minimize overlapping drivers
2026-05-12 rename all 74xx references to 74HCxx
    timings in chips-varns.v are for 74HCxx
    also added 74AHCxx and 74ACxx to chips-varns.v where available
2026-05-12 substitute in AHC and AC chips into circuit boards
    testing with clkratio=20, ie 10MHz
2026-05-12 get it working with 1.28uS cycles (clkratio=16)
    ...using AHC/AC/HC gates
2026-05-16 move dmatester to a circuit board
    ...so it has realistic propagation delays
    change TS1,TS2,TS3,TS4 times to 400nS each
    ...instead of 300,500,500,300nS each
    should be ok cuz of 74AC283s instead of 74HC283s
2026-05-17 make edge connectors all single-row 1x36
2026-05-17 place chips on extmemory board
2026-05-17 add backplane kicad pcb
2026-05-24 re-port pdp8l/zynq to pdp8i/zynq
2026-05-25 plug zynq into verimain's backplane
    simtest.tcl doesn't access any of its i/o devices yet
2026-05-25 add pdp8icmem circuit to zynq
    don't have any tests for it yet
2026-05-30 get verimain zynq code working with simtest.sh
    verimain compiles with boards and zynq code
    uses chips-varns.v for the chips
    simtest includes zynq pdp8ltty.v testing
    does not test zynq pdp8isim.v
    compiling zynq code with vivado from zynq directory
    compiles pdp8isim.v which uses the board files
2026-05-30 update zynq pdp8lfpi2c.v to continuously scan panel via i2c
2026-06-01 have simtest.sh test pdp8ifpi2c.v
    pdp8ifpi2c.v can be enabled (by clearing its 'manual' bit) to
    take over scanning the physical pidp panel via the console board.
    by default, the console board does the scanning via its internal
    counters.
    usefpi2c=0 ./simtest.sh use console board scanners (fast)
    usefpi2c=1 ./simtest.sh use pdp8ifpi2c.v scanners (slow)
2026-06-01 add ccode directory (copied from pdp8l/pipan8l directory)
    get zynq to compile and get z8ldump, z8lpanel to work with it
2026-06-03 have setsw wait for switch to soak into flipflops
    also merge pipan8lini.tcl into z8lpanelini.tcl
2026-06-05 get zynq stuff compiling
    sim mode doesn't work
2026-06-06 get zynq to run something
    $ ./z8lpanel
    z8lpanel> simon
    z8lpanel> setsw sinst 1
    z8lpanel> hardreset
    z8lpanel> isziactest
    z8lpanel> setsw sinst 0
2026-06-07 compiling ccode with x86_64 uses verilator
    run ./verizynq.x86_64 in background to simulate the zynq code
    only supports sim mode in the zynq
2026-06-07 get zynq sim reset working
    hold START+SSTEP switches down during reset
    so processor won't start (from such as CONT or lone START)
    while switches stabilize
2026-06-08 add ttyprtest simple tty printer test to z8lpanelini.tcl
    on one screen:
    $ ./z8lpanel
    > simon
    > ttyprtest
    > startat 040
    on another screen:
2026-06-08 get os8 decpack to boot
    $ ./z8lpanel
    z8lpanel> simon
    z8lpanel> source bootos8dpack.tcl
    - fix up cm_ symbol names for pin command
    - make a single instance of Z8LPage per process
    - remove os8zap references
2026-06-09 add MADR, MEAD, MAJST bus signals as inputs to FPGA
    used by z8ltc08.cc
    renamed FIELD to MEAD (extended memory address)
2026-06-12 update z8lpanel -status for PDP-8/I
2026-06-12 add pdp8irtc.v realtime clock
    also get pdp-8/v doubleroll working (twiddles SC,MQ lights)
2026-06-12 fix z8lpanel -real and -sim options
    pass them onto z8lpanelini.tcl to handle them
2026-06-12 fix z8lpanel -status state lights correctly
    the old way would glitch IAK state erratically
2026-06-13 add light/switch time jumper to console board
    fast for verilator testing
    slow for normal
2026-06-13 add debouncing to pdp8ifpi2c.v physical button scanning
2026-06-13 embolden the octal numbers on z8ipanel -status display
2026-06-15 split processor board -> procseq, proc23
    also fix z8ipanel stop button access
    and fix hardreset to always leave sstep turned off
2026-06-16 have getlb wait for i2c scan pass so lights are up-to-date
    also fix up TC08 boot timing
    tested with verizynq on PC and real Zynq
2026-06-17 get kaleid demo program working
    added video ram ip block reference to pdp8ivc8.v
    test with:
    z8ipanel kaleid.tcl e or i
2026-06-17 split remaining proc23 board into procalu and procreg
    processor is now 3 boards:
    procalu - arith/logic unit
    procreg - registers
    procseq - sequencer
2026-06-17 add os8zap circuit to zynq simulator (pdp8isim.v)
    OS/8 does a
    ISZ x
    JMP .-1
    ...during printing for a pause
    this circuit zaps it so the ISZ always reads 7777
    causing it to immediately skip over the JMP
2026-06-18 multiple lights/switches on single getlb,getsw,relsw,setsw command lines
    also remove some dead code
2026-06-18 add -killit option to z8ivc8 to kill duplicate process
2026-06-19 add a couple readme.txt files
2026-06-20 initial placement on procalu.kicad_pcb
2026-06-21 add graphics stuff to Layout.java
    not working yet
2026-06-21 add chip type checkboxes to Layout.java
2026-06-21 get Layout.java save updated layout to pcb file
2026-06-22 randomly swap sub-chips and pads within sub-chips for Layout.java
2026-06-22 remove graphics from Layout.java and get subchip/pad swapping to work
2026-06-23 have Layout.java write out pad swaps within a subchip
    ...to be applied to schematic manually
    also use filename given on Layout.java command line
    instead of using stdin/stdout
2026-06-23 partial manual routing of procalu pcb
2026-06-26 fix verisim clocking so it can test faster cycles
    verisim uses zynq.v regctld to generate pdp clock
    export clkratm1=9 # default - 100nS cycles
    export clkratm1=8 # 90nS cycles
    export clkratm1=7 # 80nS cycles (seems to work)
    export clkratm1=6 # 70nS cycles (doesn't work)
    export usefpi2c=0 or 1
2026-06-27 some more manual routine procalu board
2026-06-27 procalu board routed
